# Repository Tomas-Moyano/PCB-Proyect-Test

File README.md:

# PCB-Proyect-Test
Un repositorio para explorar las posibilidades de GIT a medida que se desarrolla un PCB desde cero en KiCAD

Objetivo:
Aprender el flujo de trabajo en el proceso de crear un PCB que recibe modificaciones/evoluciones
y poder llevar un control de sus versiones.

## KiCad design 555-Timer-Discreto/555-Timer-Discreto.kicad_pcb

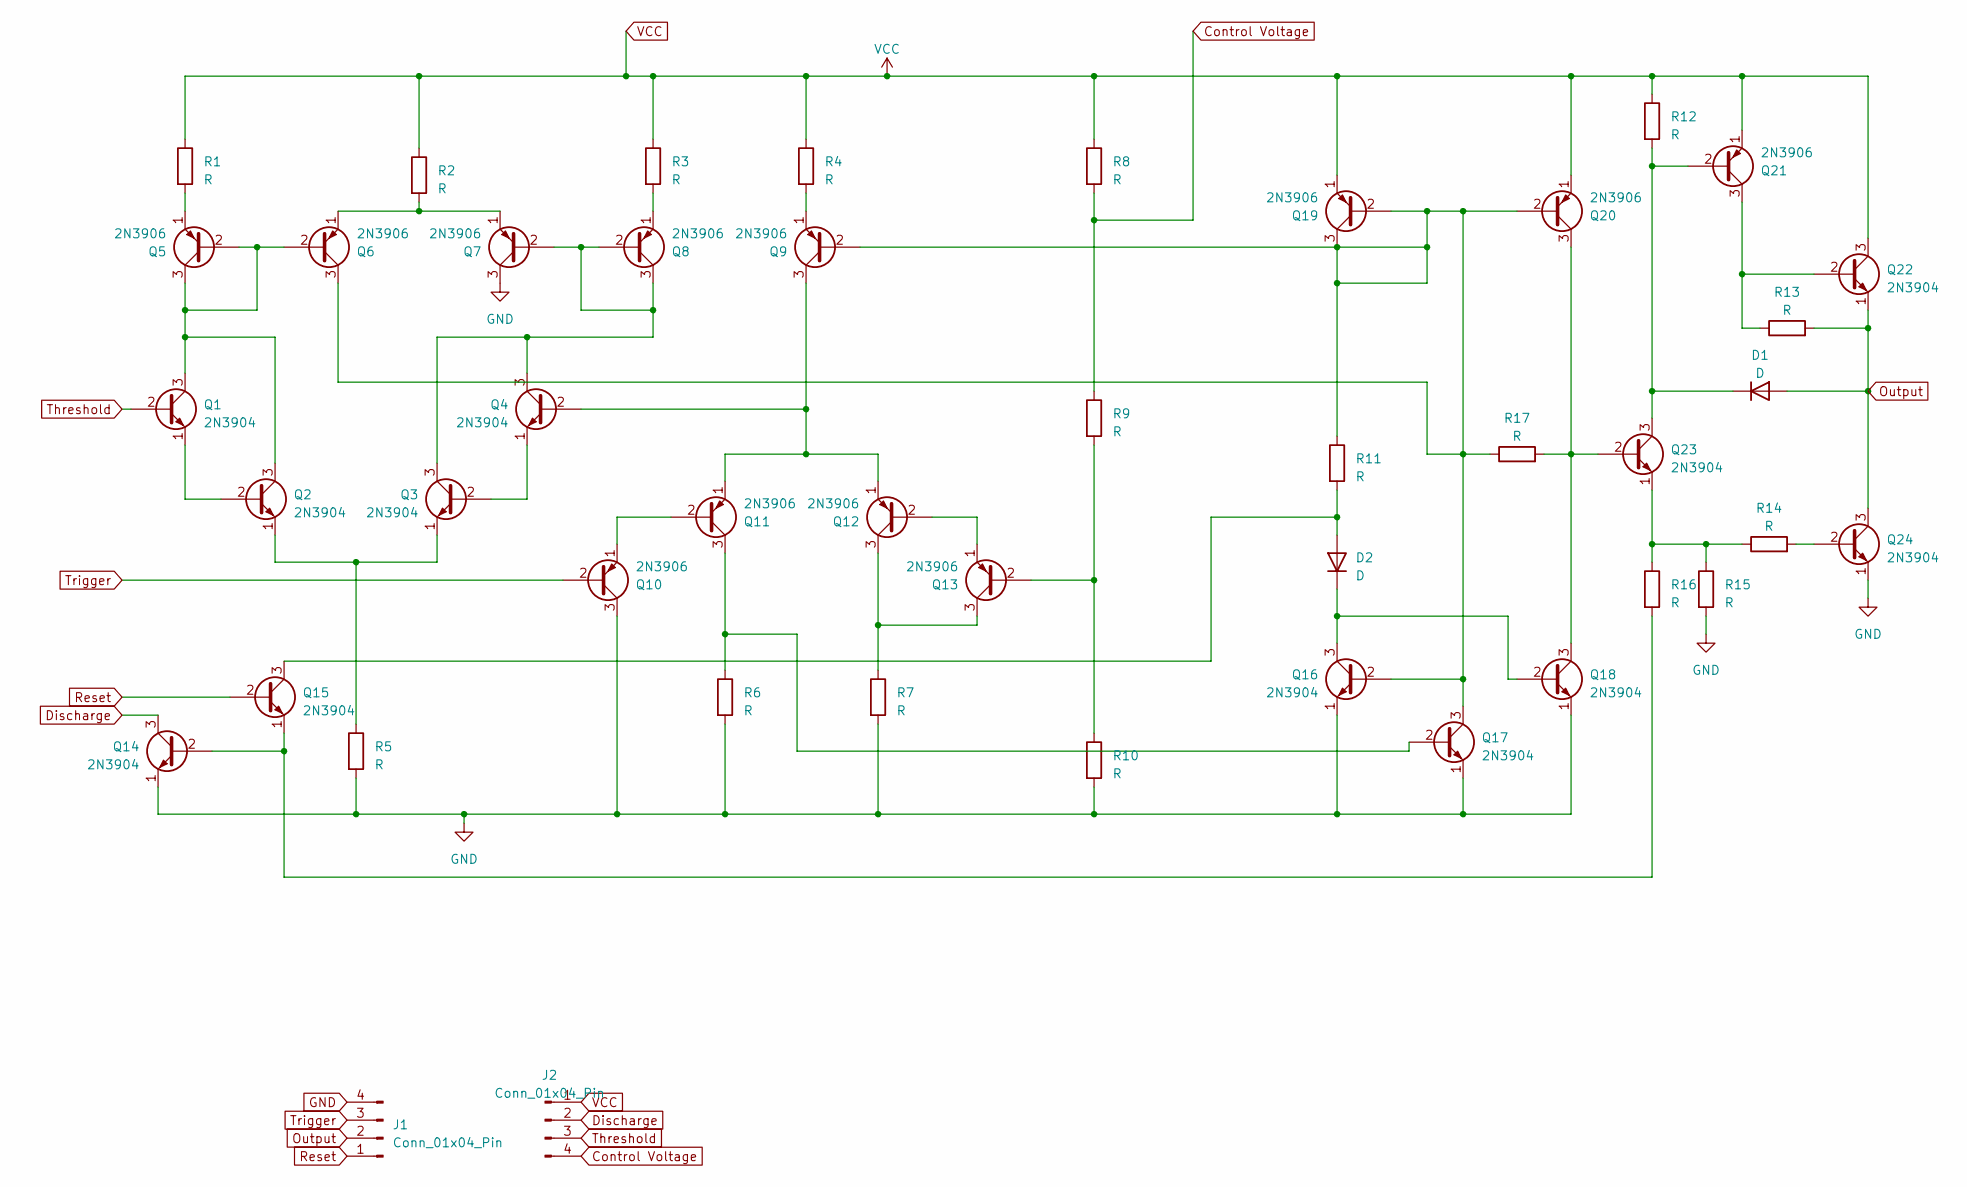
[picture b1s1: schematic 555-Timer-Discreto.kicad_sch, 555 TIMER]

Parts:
D1, D2: D; D_A-405_P7.62mm_Horizontal
J1, J2: Conn_01x04_Pin; PinHeader_1x04_P2.54mm_Vertical
Q1, Q2, Q3, Q4, Q14, Q15, Q16, Q17, Q18, Q22, Q23, Q24: 2N3904; TO-92_Inline
Q5, Q6, Q7, Q8, Q9, Q10, Q11, Q12, Q13, Q19, Q20, Q21: 2N3906; TO-92_Inline
R1, R2, R3, R4, R5, R6, R7, R8, R9, R10, R11, R12, R13, R14, R15, R16, R17: R; R_Axial_DIN0204_L3.6mm_D1.6mm_P5.08mm_Horizontal

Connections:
Control Voltage: J2.4, R8.2, R9.1
Discharge: J2.2, Q14.3 (C)
GND: J1.4, Q7.3 (C), Q10.3 (C), Q14.1 (E), Q16.1 (E), Q17.1 (E), Q18.1 (E), Q24.1 (E), R5.2, R6.2, R7.2, R10.2, R15.2
unnamed: D1.1 (K), Q21.2 (B), Q23.3 (C), R12.2
unnamed: D2.2 (A), Q15.3 (C), R11.2
unnamed: D2.1 (K), Q16.3 (C), Q18.2 (B)
unnamed: Q1.3 (C), Q2.3 (C), Q5.2 (B), Q5.3 (C), Q6.2 (B)
unnamed: Q1.1 (E), Q2.2 (B)
unnamed: Q2.1 (E), Q3.1 (E), R5.1
unnamed: Q3.2 (B), Q4.1 (E)
unnamed: Q3.3 (C), Q4.3 (C), Q7.2 (B), Q8.2 (B), Q8.3 (C)
unnamed: Q5.1 (E), R1.2
unnamed: Q6.1 (E), Q7.1 (E), R2.2
unnamed: Q8.1 (E), R3.2
unnamed: Q9.1 (E), R4.2
unnamed: Q10.1 (E), Q11.2 (B)
unnamed: Q11.3 (C), Q17.2 (B), R6.1
unnamed: Q4.2 (B), Q9.3 (C), Q11.1 (E), Q12.1 (E)
unnamed: Q12.2 (B), Q13.1 (E)
unnamed: Q12.3 (C), Q13.3 (C), R7.1
unnamed: Q13.2 (B), R9.2, R10.1
unnamed: Q14.2 (B), Q15.1 (E), R16.2
unnamed: Q6.3 (C), Q9.2 (B), Q16.2 (B), Q17.3 (C), Q19.2 (B), Q19.3 (C), Q20.2 (B), R11.1, R17.1
unnamed: Q18.3 (C), Q20.3 (C), Q23.2 (B), R17.2
unnamed: Q21.3 (C), Q22.2 (B), R13.1
unnamed: Q23.1 (E), R14.1, R15.1, R16.1
unnamed: Q24.2 (B), R14.2
Output: D1.2 (A), J1.2, Q22.1 (E), Q24.3 (C), R13.2
Reset: J1.1, Q15.2 (B)
Threshold: J2.3, Q1.2 (B)
Trigger: J1.3, Q10.2 (B)
VCC: J2.1, Q19.1 (E), Q20.1 (E), Q21.1 (E), Q22.3 (C), R1.1, R2.1, R3.1, R4.1, R8.1, R12.1

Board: 2 copper layers, 45 parts (0 on the bottom side), 32 nets, no tracks yet.

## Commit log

2023-10-07 Componentes
    Se agregaron los TRANSISTORES al diagrama.
    Faltan las RESISTENCIAS.
2023-10-09 Se incorporaron el resto de los componentes y se hicieron las conexiones pertinentes
2023-10-10 Se asignaron huellas a los componentes
2023-10-11 Esquemático terminando
    Esquemático: se agregaron los conectores y etiquetas de los pines de salida.
    PCB: comenzó la organización de los componentes en el espacio físico
